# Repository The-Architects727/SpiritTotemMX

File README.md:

# SpiritTotemMX

A port of the [TOTEM](https://github.com/GEIGEIGEIST/TOTEM) split keyboard
to MX-style hot-swap switches, with a few of my own additions (per-half
battery-charge LEDs on the dongle, an on-demand battery check, and sleep
management for each half — see [Firmware](#firmware)).

This repo has everything needed to build one from scratch: the 3D-printable
case, the PCB design and fabrication files, ready-to-flash firmware, and
the full assembly guide below.

The layout is inspired by the original TOTEM — a printed test of that
shape was comfortable enough for my hands that I built the rest of this
board around it, redesigning the PCB and case for MX switches from
scratch. The XIAO boards sit on hot-swap headers rather than being
soldered in directly, so they can move to a different project later if
needed. Currently FDM printed in PLA with no tenting solution yet — both
are on the list for a future revision.

## Contents

- [What's in this repo](#whats-in-this-repo)
- [Bill of materials](#bill-of-materials)
- [Assembly](#assembly)
- [Keymap](#keymap)
- [Firmware](#firmware)
- [License](#license)

## What's in this repo

| Folder | Contents |
|---|---|
| [`Case/`](Case) | STL files for 3D printing the case and keycaps |
| [`PCB/`](PCB) | KiCad project source and fabrication-ready Gerbers/BOM/positions |
| [`Firmware/`](Firmware) | Pre-built `.uf2` firmware, ready to flash |

## Bill of materials

Links are the specific listings used for this build, not strict
requirements — quantities are usually a bulk pack, and most of these have
plenty of equivalent alternatives if a listing goes stale.

- 1 PCB — the left half, right half, and dongle are all panelized onto a
  single board you order as one piece (see [`PCB/`](PCB))
- 38× key switches — [Keychron Super Switch, tactile, 110-pack](https://www.amazon.com/dp/B0F9FJDWGZ)
- 38× Kailh hot-swap sockets — [Kailh CPG151101S11, 50-pack](https://www.amazon.com/dp/B0BVH6M5FP)
- 38× diodes (through-hole or SMD) — [1N4001, DO-41, 120-pack](https://www.amazon.com/dp/B0DN5YNFHQ)
  (1N4148 is the more common choice for keyboard matrices, but 1N4001 works
  fine here too)
- 3× Seeed Studio XIAO nRF52840 boards, with headers on —
  [Seeed Studio, 3-pack](https://www.seeedstudio.com/Seeed-Studio-XIAO-nRF52840-3PCS-p-5921.html)
- 2× JST 2.0 female wire connectors (battery leads for the two hand boards)
  and 4× JST 2.0 male PCB connectors — one kit covers both:
  [JST-PH 2.0mm 2-pin, male+female with 10cm wire, 20 sets](https://www.amazon.com/dp/B0D7Q9HJLQ)
- 2× through-hole PCB slide switches (mounted sideways so they poke out the
  side of the case) — [Chanzon SPDT 3mm slide switch, 70-pack](https://www.amazon.com/dp/B09R43HCY3)
- 2.54mm pitch headers for the XIAO standoffs — 60 pin positions total —
  [2.54mm male/female pin headers, 30-pack](https://www.amazon.com/dp/B0FCTSSLK9)
- 2× 3.7V JST 2.0 batteries, no more than 7mm thick × 20mm wide × 45mm long —
  [AKZYTUE 3.7V 750mAh LiPo, JST PH2.0](https://www.amazon.com/dp/B07TWHFW82)
- 2× 5mm LEDs
- 2× 330Ω resistors (through-hole or SMD)
- M2 brass heat-set inserts —
  [Pofsnnx M2 brass heat-set inserts, 250-pack](https://www.amazon.com/dp/B0FJXLNMLM)
- M2 screws: 6× 12mm, 1× 4mm —
  [KADRICK M2 hex socket button head screw assortment, 1000-pack](https://www.amazon.com/dp/B0DRCG3418)

## Assembly

### PCB and soldering

1. Break the panelized PCB apart into its 3 boards (left, right, dongle)
   along the mouse-bite tabs, and lightly sand the broken edges smooth.
2. Solder the diodes to the **top** face and the hot-swap sockets to the
   **underside**. The switchplate has cutouts to clear the diodes as long
   as they're soldered close to the board.
3. Solder the 2.54mm headers to the top face of each hand's board, where
   the XIAO will sit.
4. Solder the JST connectors and the slide power switch into place.
5. Solder a JST female connector pigtail to the underside of each hand's
   XIAO board, for its battery. This is the fiddliest step — put a small
   blob of solder on the pad first, then push the wire into the molten
   blob with the iron in one hand and a small pair of pliers in the other.
6. For the dongle: solder on the headers, then solder the two 5mm LEDs to
   the underside so they shine from the inside toward the outside edge,
   along with their resistors.

### Case

- `Top.stl` and `Bottom.stl` are single files — print one of each and
  mirror a second copy of each in your slicer for the other hand.
  `Switchplate.stl` and `Switchplate-left.stl` are **not** mirror images of
  each other — print each one exactly once.
- [`Case/KeyCaps/`](Case/KeyCaps) has the keycap profiles, designed to be
  printed flat on the bed while still having a swept (sculpted) profile —
  no supports needed despite the curve. Print 12× `Home`, 20×
  `Top-Bottom`, and 6× `Thumb` (38 keycaps total).
- Press a 2mm brass insert into the hole in the dongle base's dovetail.
- Press a heat-set insert into every standoff hole in each hand's bottom
  case piece.
- **Dongle:** drop the PCB+XIAO assembly into the bottom housing, slide the
  top piece on and push it forward to lock the board in place, then secure
  with a single M2×4mm screw.
- **Each hand:** place the PCB on the bottom case, then the switchplate
  over it (press a few switches into place to hold the sandwich together
  while you work), then the top plate, and secure with a 12–16mm screw in
  each top hole.

### First power-on

The dongle learns which half is "left" and which is "right" by whichever
one it bonds to first — so the very first time, power things on in this
order:

1. Everything off.
2. Plug in the dongle.
3. Power on the **left** half, and wait a moment.
4. Power on the **right** half.

After this first pairing, the two halves can be powered on in any order.

## Keymap

Colemak-DH based, 5 layers. `...` means "transparent" (falls through to
the layer below). A printable version with a visual key-by-key diagram of
every layer is at [`keymap-reference.pdf`](keymap-reference.pdf).

### Base

```
  Q      W      F      P      B        J      L      U      Y      '
  A      R      S      T      G        M      N      E      I      O
 Esc     Z      X      C      D      V        K      H      ,      .      /      -
   Ctrl/Del  Nav/Tab    Space     Shift/Ent  Sym/Bspc   Fun/\
```

### Nav

*Hold the left thumb's `Nav/Tab` key.*

```
 ...    ...    ...    ...    ...      ...    Home    Up    PgUp   End
 Gui    Alt    Ctrl   ...    ...      Del    Left   Down  Right   PgDn
 ...    ...    ...    ...    ...    ...      Ins    ...    ...    ...    ...    ...
     ...       ...       ...         ...       ...       ...
```

### Sym

*Hold the right thumb's `Sym/Bspc` key.*

```
  1      2      3      4      5        6      7      8      9      0
  !      @      #      $      %        ^      &      *      (      )
Studio   (      [      {      <      `        ~      >      }      ]      )     ...
     ...       ...       ...         ...       ...       ...
```

### Fun

*Hold the right thumb's `Fun/\` key.*

```
  F1     F2     F3     F4     F5       F6     F7     F8     F9    F10
 ...    ...    ...    ...    ...      ...    ...    ...    F11    F12
BatChk  Boot   ...    ...    ...    ...      ...    ...    ...    ...   ToGame  ...
     ...       ...       ...         ...       ...       ...
```

`BatChk` blinks the dongle's LEDs to report each half's battery charge in
10% steps. `Boot` reboots that half into its UF2 bootloader. `ToGame`
switches to the Game layer.

### Game

*Toggled from Fun's `ToGame` key; `ToBase` returns to Base.*

```
  T      Q      X      E      R        Y      U      I      O      P
  G      A      W      D      F        H      J      K      L      ;
 ...     B      Z      S      C      V        N      M      ,      .      /     ...
    Shift      Ctrl     Space       Enter      Bspc     ToBase
```

QWERTY, except W/S/X are rotated one column so A, W, and D all land on the
home row together with S directly beneath — this columnar layout puts W a
row above A/D by default, which doesn't rest as naturally for WASD as a
traditional keyboard's row stagger does. X moves up to W's old spot. The
thumb cluster is set up for typical games (Shift, Ctrl, Space on the left;
Enter, Backspace on the right) rather than mod-taps, since a key's brief
"tap" behavior is exactly the kind of thing you don't want fighting with
WASD-style movement.

## Firmware

[`Firmware/Colemak/`](Firmware/Colemak) has four ready-to-flash `.uf2`
files — one each for the left half, right half, dongle, and a
`settings_reset` image used to clear Bluetooth pairings if you ever need
to re-pair from scratch.

**To flash a board:** plug it into USB, double-tap its reset button to
drop it into bootloader mode (it shows up as a USB drive), then drag the
matching `.uf2` file onto that drive. Flash all three main boards; only
use `settings_reset` if you need to re-pair.

This firmware also includes a few extras beyond the stock TOTEM build:
per-half battery-charge LEDs on the dongle, an on-demand battery-level
check from the keyboard itself, and independent sleep for each half (with
a warning flash) that's triggered either manually or automatically when
the dongle's out of reach.

**Want to build it yourself, or modify it?** The buildable source and
GitHub Actions build workflow live in a separate repo,
[zmk-config-spirittotem](https://github.com/The-Architects727/zmk-config-spirittotem),
released under the MIT license.

## License

- **Case and PCB** (everything in [`Case/`](Case) and [`PCB/`](PCB)) are
  licensed [CC BY-SA 4.0](LICENSE): use, modify, and share freely, with
  credit, and any modified version you share stays under the same license.
- **Firmware** is not included as source here (see [Firmware](#firmware)) —
  the buildable source lives in
  [zmk-config-spirittotem](https://github.com/The-Architects727/zmk-config-spirittotem)
  under the MIT license. The pre-built `.uf2` binaries in
  [`Firmware/Colemak/`](Firmware/Colemak) are just compiled output from
  that source.

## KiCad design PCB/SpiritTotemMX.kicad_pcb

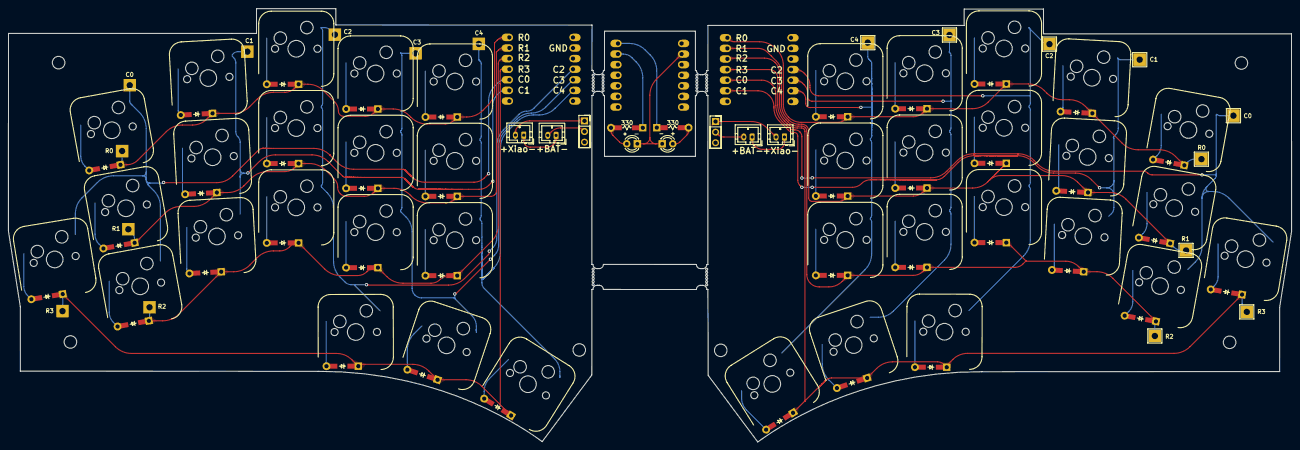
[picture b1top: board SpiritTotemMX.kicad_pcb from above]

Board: 2 copper layers, 307.3 x 103.8 mm, 87 parts (0 on the bottom side), 64 nets.

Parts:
D1, D2, D3, D3#2, D3#3, D4, D5, D6, D7, D8, D9, D10, D11, D12, D13, D14, D15, D16, D17, D18, D19, D20, D21, D22, D23, D24, D25, D26, D27, D28, D29, D30, D31, D32, D33, D34, D35, D36, D37, D38: ComboDiode-SOD-Through
L_Bat_Bat: JST_PH_B2B-PH-K_1x02_P2.00mm_Vertical
L_Switch_Socket: PinSocket_1x03_P2.54mm_Vertical
L_Xiao_Bat: JST_PH_B2B-PH-K_1x02_P2.00mm_Vertical
R_Bat_Bat: JST_PH_B2B-PH-K_1x02_P2.00mm_Vertical
R_Switch_Socket: PinSocket_1x03_P2.54mm_Vertical
R_Xiao_Bat: JST_PH_B2B-PH-K_1x02_P2.00mm_Vertical
S1, S2, S3, S4, S5, S6, S7, S8, S9, S10, S11, S12, S13, S14, S15, S16, S17, S18, S19, S20, S21, S22, S23, S24, S25, S26, S27, S28, S29, S30, S31, S32, S33, S34, S35, S36, S37, S38: MX-ergogen
U?: xiao-ble-thruhole; xiao-ble-tht
U?#2, U?#3: xiao-ble-thruhole; xiao-ble-tht

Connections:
Dongle_L: D3#3.1, U?#2.2
Dongle_R: D3#2.1, U?#2.1
L_Bat+: L_Switch_Socket.1, L_Switch_Socket.3, L_Xiao_Bat.2
L_Bat-: L_Bat_Bat.1, L_Xiao_Bat.1
L_Batery+: L_Bat_Bat.2, L_Switch_Socket.2
L_Col0: S32.2, S33.2, S34.2, S35.2, U?.5
L_Col1: S29.2, S30.2, S31.2, U?.6
L_Col2: S26.2, S27.2, S28.2, S36.2, U?.11
L_Col3: S23.2, S24.2, S25.2, S37.2, U?.10
L_Col4: S20.2, S21.2, S22.2, S38.2, U?.9
L_Row0: D22.1, D25.1, D28.1, D31.1, D34.1, U?.1
L_Row1: D21.1, D24.1, D27.1, D30.1, D33.1, U?.2
L_Row2: D20.1, D23.1, D26.1, D29.1, D32.1, U?.3
L_Row3: D35.1, D36.1, D37.1, D38.1, U?.4
R_Bat+: R_Switch_Socket.1, R_Switch_Socket.3, R_Xiao_Bat.2
R_Bat-: R_Bat_Bat.1, R_Xiao_Bat.1
R_Batery+: R_Bat_Bat.2, R_Switch_Socket.2
R_Col0: S13.2, S14.2, S15.2, S16.2, U?#3.5
R_Col1: S10.2, S11.2, S12.2, U?#3.6
R_Col2: S7.2, S8.2, S9.2, S17.2, U?#3.11
R_Col3: S4.2, S5.2, S6.2, S18.2, U?#3.10
R_Col4: S1.2, S2.2, S3.2, S19.2, U?#3.9
R_Row0: D3.1, D6.1, D9.1, D12.1, D15.1, U?#3.1
R_Row1: D2.1, D5.1, D8.1, D11.1, D14.1, U?#3.2
R_Row2: D1.1, D4.1, D7.1, D10.1, D13.1, U?#3.3
R_Row3: D16.1, D17.1, D18.1, D19.1, U?#3.4
left_matrix_index_bottom: D23.2, S23.1
left_matrix_index_home: D24.2, S24.1
left_matrix_index_top: D25.2, S25.1
left_matrix_inner_bottom: D20.2, S20.1
left_matrix_inner_home: D21.2, S21.1
left_matrix_inner_top: D22.2, S22.1
left_matrix_middle_bottom: D26.2, S26.1
left_matrix_middle_home: D27.2, S27.1
left_matrix_middle_top: D28.2, S28.1
left_matrix_pinky_bottom: D32.2, S32.1
left_matrix_pinky_home: D33.2, S33.1
left_matrix_pinky_top: D34.2, S34.1
left_matrix_ring_bottom: D29.2, S29.1
left_matrix_ring_home: D30.2, S30.1
left_matrix_ring_top: D31.2, S31.1
left_pinky_outer_a_key: D35.2, S35.1
left_thumb_inner_a_thumb: D36.2, S36.1
left_thumb_mid_a_thumb: D37.2, S37.1
left_thumb_outer_a_thumb: D38.2, S38.1
right_matrix_index_bottom: D4.2, S4.1
right_matrix_index_home: D5.2, S5.1
right_matrix_index_top: D6.2, S6.1
right_matrix_inner_bottom: D1.2, S1.1
right_matrix_inner_home: D2.2, S2.1
right_matrix_inner_top: D3.2, S3.1
right_matrix_middle_bottom: D7.2, S7.1
right_matrix_middle_home: D8.2, S8.1
right_matrix_middle_top: D9.2, S9.1
right_matrix_pinky_bottom: D13.2, S13.1
right_matrix_pinky_home: D14.2, S14.1
right_matrix_pinky_top: D15.2, S15.1
right_matrix_ring_bottom: D10.2, S10.1
right_matrix_ring_home: D11.2, S11.1
right_matrix_ring_top: D12.2, S12.1
right_pinky_outer_a_key: D16.2, S16.1
right_thumb_inner_a_thumb: D17.2, S17.1
right_thumb_mid_a_thumb: D18.2, S18.1
right_thumb_outer_a_thumb: D19.2, S19.1

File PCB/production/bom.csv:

Designator,Footprint,Quantity,Value,LCSC Part #
"_9, _8, _7, _6, _5, _4, _3, _2, ",,9,,
"D1, D10, D11, D12, D13, D14, D15, D16, D17, D18, D19, D2, D20, D21, D22, D23, D24, D25, D26, D27, D28, D29, D3_3, D3_2, D3, D30, D31, D32, D33, D34, D35, D36, D37, D38, D4, D5, D6, D7, D8, D9",ComboDiode-SOD-Through,40,,
"L_BAT_BAT, L_XIAO_BAT, R_BAT_BAT, R_XIAO_BAT",JST_PH_B2B-PH-K_1x02_P2.00mm_Vertical,4,JST_PH_B2B-PH-K_1x02_P2.00mm_Vertical,
"L_SWITCH_SOCKET, R_SWITCH_SOCKET",PinSocket_1x03_P2.54mm_Vertical,2,PinSocket_1x03_P2.54mm_Vertical,
"S1, S10, S11, S12, S13, S14, S15, S16, S17, S18, S19, S2, S20, S21, S22, S23, S24, S25, S26, S27, S28, S29, S3, S30, S31, S32, S33, S34, S35, S36, S37, S38, S4, S5, S6, S7, S8, S9",MX-ergogen,38,,
"U?_3, U?_2, U?",xiao-ble-tht,3,xiao-ble-thruhole,
